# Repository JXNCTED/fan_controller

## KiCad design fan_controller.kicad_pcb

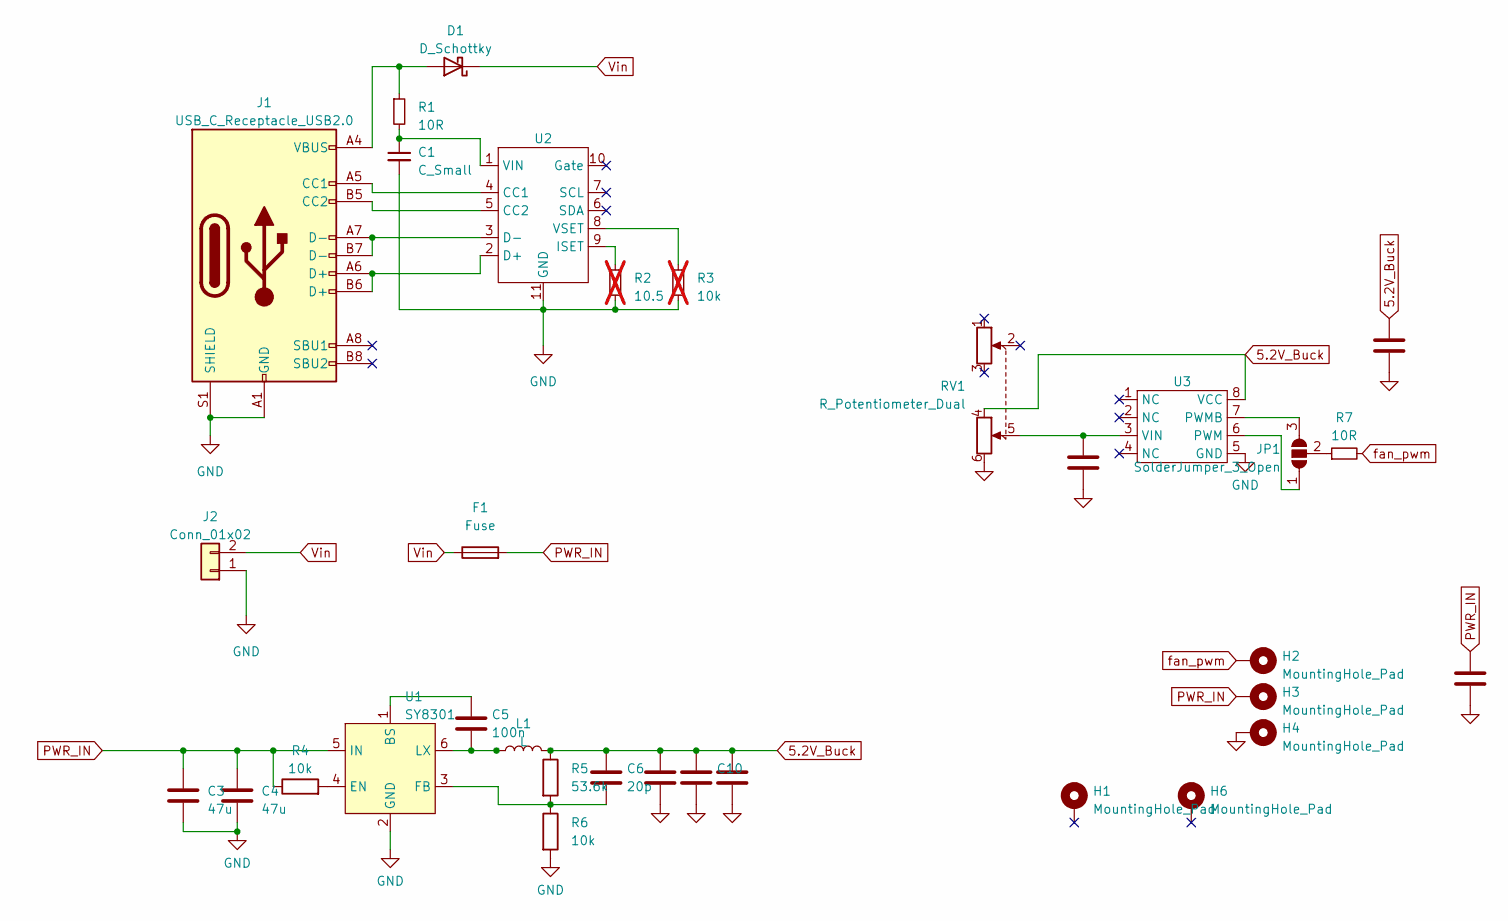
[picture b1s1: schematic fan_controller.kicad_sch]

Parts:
C1: C_Small; C_0603_1608Metric
C2, C7, C8: C_0603_1608Metric
C3, C4: 47u; C_1206_3216Metric
C5: 100n; C_0603_1608Metric
C6: 20p; C_0603_1608Metric
C9, C10, C11: C_1206_3216Metric
D1: D_Schottky; D_SMF
F1: Fuse; Fuse_1210_3225Metric
H1, H6: MountingHole_Pad; MountingHole_4.5mm_Pad_Via
H2, H3, H4: MountingHole_Pad; pad
J1: USB_C_Receptacle_USB2.0; USB_C_Receptacle_Palconn_UTC16-G
J2: Conn_01x02; AMASS_XT30PW-M_1x02_P2.50mm_Horizontal
JP1: SolderJumper_3_Open; SolderJumper-3_P2.0mm_Open_TrianglePad1.0x1.5mm_NumberLabels
L1: L; L_Bourns-SRN4018
R1, R7: 10R; R_0603_1608Metric
R2: 10.5; R_0603_1608Metric; not fitted
R3: 10k; R_0603_1608Metric; not fitted
R4, R6: 10k; R_0603_1608Metric
R5: 53.6k; R_0603_1608Metric
RV1: R_Potentiometer_Dual; Potentiometer_Alps_RK097_Dual_Horizontal
U1: SY8301; SOT-23-6
U2: DFN-10-1EP_3x3mm_P0.5mm_EP1.55x2.48mm
U3: SOP-8_3.9x4.9mm_P1.27mm

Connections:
5.2V_Buck: C2.1, C6.1, C9.1, C10.1, C11.1, L1.2, R5.1, RV1.4, U3.8 (VCC)
GND: C1.2, C2.2, C3.2, C4.2, C7.2, C8.2, C9.2, C10.2, C11.2, H4.1, J1.A1 (GND), J1.A12 (GND), J1.B1 (GND), J1.B12 (GND), J1.S1 (SHIELD), J2.1, R2.2, R3.2, R6.2, RV1.6, U1.2 (GND), U2.11 (GND), U3.5 (GND)
unnamed: D1.2 (A), J1.A4 (VBUS), J1.A9 (VBUS), J1.B4 (VBUS), J1.B9 (VBUS), R1.1
unnamed: J1.A5 (CC1), U2.4 (CC1)
unnamed: J1.B5 (CC2), U2.5 (CC2)
unnamed: JP1.1 (A), U3.6 (PWM)
unnamed: JP1.3 (B), U3.7 (PWMB)
unnamed: JP1.2 (C), R7.1
unnamed: C5.1, U1.1 (BS)
unnamed: R4.2, U1.4 (EN)
unnamed: C6.2, R5.2, R6.1, U1.3 (FB)
unnamed: C5.2, L1.1, U1.6 (LX)
unnamed: J1.A6 (D+), J1.B6 (D+), U2.2 (D+)
unnamed: J1.A7 (D-), J1.B7 (D-), U2.3 (D-)
unnamed: R2.1, U2.9 (ISET)
unnamed: C1.1, R1.2, U2.1 (VIN)
unnamed: R3.1, U2.8 (VSET)
unnamed: C8.1, RV1.5, U3.3 (VIN)
PWR_IN: C3.1, C4.1, C7.1, F1.2, H3.1, R4.1, U1.5 (IN)
Vin: D1.1 (K), F1.1, J2.2
fan_pwm: H2.1, R7.2

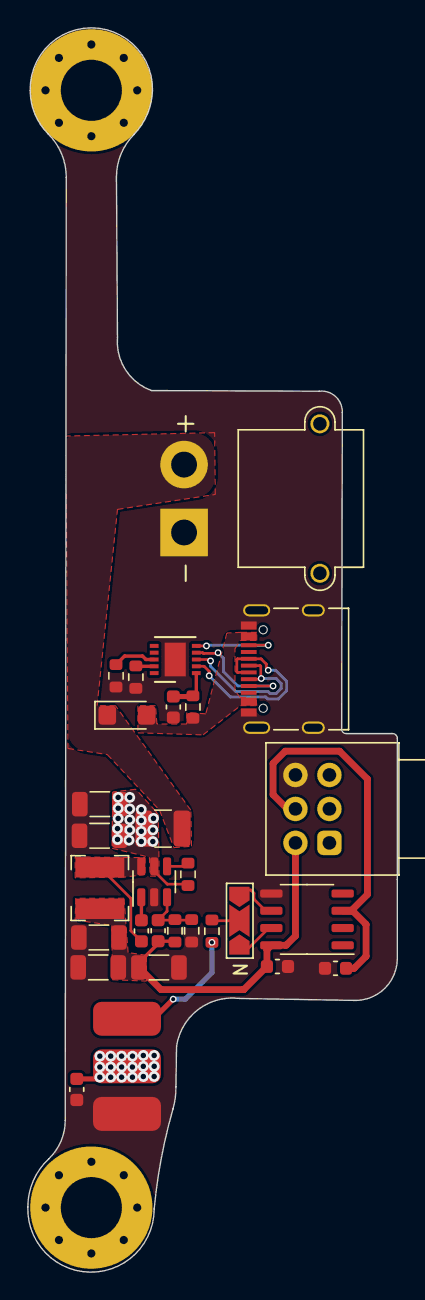
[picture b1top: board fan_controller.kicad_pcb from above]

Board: 2 copper layers, 27.2 x 91.6 mm, 33 parts (0 on the bottom side), 21 nets.

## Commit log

2023-06-22 init repo
2023-06-22 add project
2023-06-22 test github workflow
2023-06-22 install dependency
2023-06-22 test
